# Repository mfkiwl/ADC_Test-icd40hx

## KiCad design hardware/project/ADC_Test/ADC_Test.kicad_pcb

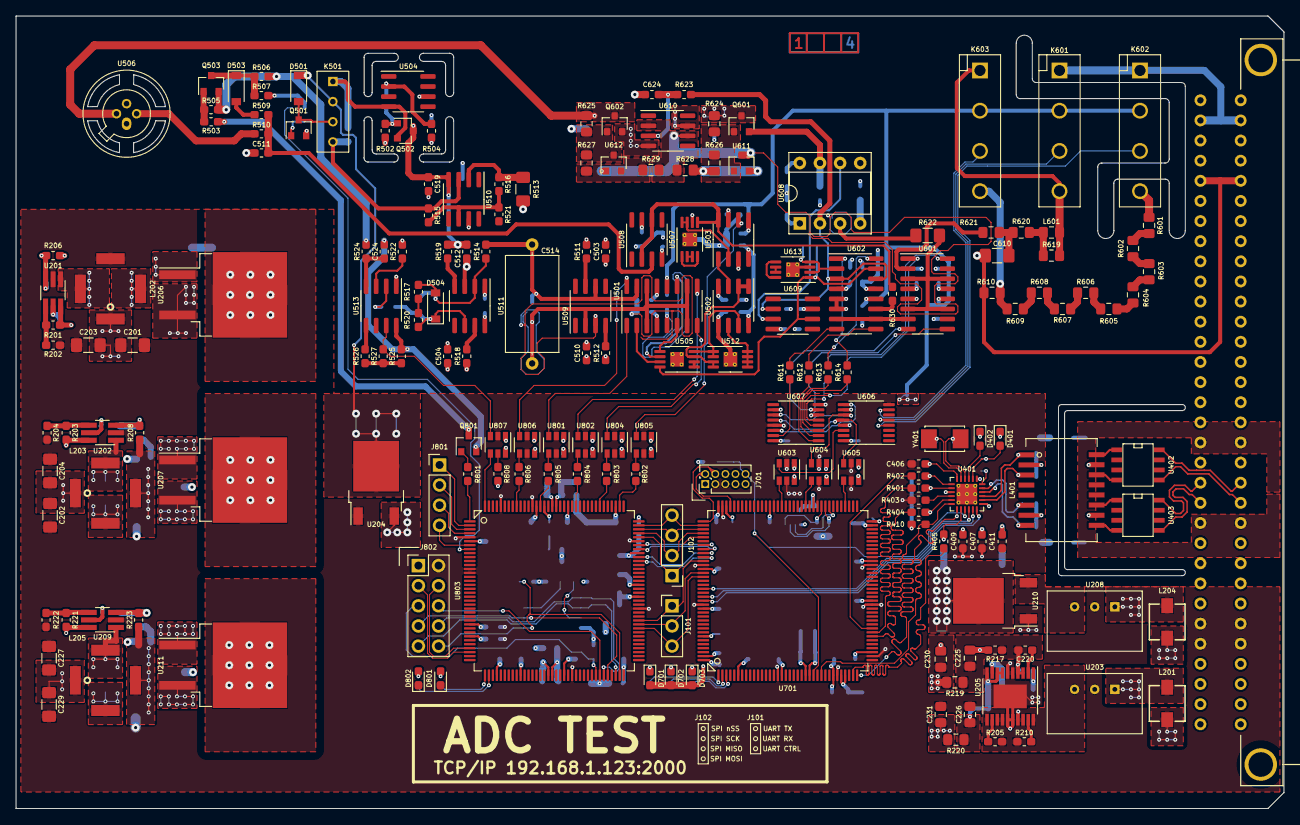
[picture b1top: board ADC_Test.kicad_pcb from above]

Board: 4 copper layers, 160.0 x 100.0 mm, 383 parts (0 on the bottom side), 257 nets.

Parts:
C201, C202, C205, C206, C224, C227, C228: 10u/50V; C_1206_3216Metric_Pad1.42x1.75mm_HandSolder
C203, C204, C216, C217, C218, C219, C222, C223, C229, C243, C244, C245: 4u7/50V; C_1206_3216Metric_Pad1.42x1.75mm_HandSolder
C207, C208, C232, C233, C235, C406, C407, C711, C720: 1u; C_0603_1608Metric_Pad1.05x0.95mm_HandSolder
C209, C210, C238: 1u/HC; C_1206_3216Metric_Pad1.42x1.75mm_HandSolder
C211, C234: 10u/16V; C_1206_3216Metric_Pad1.42x1.75mm_HandSolder
C212, C225, C230, C231, C827, C829: 10u; C_0805_2012Metric_Pad1.15x1.40mm_HandSolder
C213, C241: 47u/16V; C_1206_3216Metric_Pad1.42x1.75mm_HandSolder
C214, C215, C242: 4p7; C_0603_1608Metric_Pad1.05x0.95mm_HandSolder
C220, C221, C239, C240: 10n; C_0603_1608Metric_Pad1.05x0.95mm_HandSolder
C226: 4u7; C_0805_2012Metric_Pad1.15x1.40mm_HandSolder
C236, C237, C402, C405, C408, C409, C410, C411, C412, C502, C503, C504, C505, C506, C507, C508, C509, C510, C511, C512, C513, C516, C517, C518, C519, C520, C523, C524, C601, C602, C603, C604, C605, C606, C607, C608, C609, C611, C612, C613, C614, C615, C616, C617, C618, C619, C620, C621, C622, C623, C701, C702, C703, C705, C708, C710, C712, C713, C714, C715, C716, C717, C718, C719, C721, C801, C802, C803, C804, C805, C806, C807, C808, C809, C810, C811, C812, C813, C814, C815, C816, C817, C818, C819, C820, C821, C822, C823, C824, C825, C826, C828, C830: 100n; C_0603_1608Metric_Pad1.05x0.95mm_HandSolder
C401, C404, C704, C706: 8p; C_0603_1608Metric_Pad1.05x0.95mm_HandSolder
C403: 470p; C_0603_1608Metric_Pad1.05x0.95mm_HandSolder
C413, C414: 1n/1kV; C_1206_3216Metric_Pad1.42x1.75mm_HandSolder
C501: 10p; C_0603_1608Metric_Pad1.05x0.95mm_HandSolder
C514: 23PS222; C_Axial_L12.0mm_D6.5mm_P15.00mm_Horizontal
C515: 2n2/SMD; C_0603_1608Metric_Pad1.05x0.95mm_HandSolder
C521: 33p; C_0603_1608Metric_Pad1.05x0.95mm_HandSolder
C522: DNP; C_0603_1608Metric_Pad1.05x0.95mm_HandSolder
C610: 4n7; C_1206_3216Metric_Pad1.42x1.75mm_HandSolder
C624, C625: 4n7; C_0603_1608Metric_Pad1.05x0.95mm_HandSolder
C707, C709: 2u2; C_0805_2012Metric_Pad1.15x1.40mm_HandSolder
D201, D202, D203: PMEG6010EP,115; D_SOD-128
D401: YELLOW; LED_0603_1608Metric_Pad1.05x0.95mm_HandSolder
D402, D702, D801: GREEN; LED_0603_1608Metric_Pad1.05x0.95mm_HandSolder
D501: 1N4148W; D_SOD-123
D502: BZT585B15TQ-13; D_SOD-523
D503, D504, D505: BAV21W; D_SOD-123
D701, D802: RED; LED_0603_1608Metric_Pad1.05x0.95mm_HandSolder
D703: BLUE; LED_0603_1608Metric_Pad1.05x0.95mm_HandSolder
D803: CDBU0520; D_SOD-523
FB401, FB701: 742792031; L_0805_2012Metric_Pad1.15x1.40mm_HandSolder
J101: Conn_01x03_Male; PinHeader_1x03_P2.54mm_Vertical
J102, J801: Conn_01x04_Male; PinHeader_1x04_P2.54mm_Vertical
J301: C64AC; Socket_DIN41612-CaseC1-AC-Male-64Pin-2rows
J701: 20021111-00010T4LF; PinHeader_2x05_P1.27mm_Vertical
J802: Conn_02x05; PinHeader_2x05_P2.54mm_Vertical
K501: 9012
K601, K602, K603: HE3621A0510; HE360_x-5050462-8
L201, L204: TCK-141
L202, L203, L205: 74489440068
L401: 749010012A
L601: L0805R100MPWRT; R_0805_2012Metric_Pad1.15x1.40mm_HandSolder
Q501, Q503, Q601: BC847; SOT-23
Q502: MMBTA55; SOT-23
Q602, Q801: BC857; SOT-23
R201, R203, R205, R206, R208, R210, R221, R223: 1M; R_0603_1608Metric_Pad1.05x0.95mm_HandSolder
R202, R204, R222: 287k; R_0603_1608Metric_Pad1.05x0.95mm_HandSolder
R207: 82k5; R_0603_1608Metric_Pad1.05x0.95mm_HandSolder
R209: 39k2; R_0603_1608Metric_Pad1.05x0.95mm_HandSolder
R211, R212: 1k6; R_0603_1608Metric_Pad1.05x0.95mm_HandSolder
R213, R214, R226: 120; R_0603_1608Metric_Pad1.05x0.95mm_HandSolder
R215: 357k; R_0603_1608Metric_Pad1.05x0.95mm_HandSolder
R216: 210k; R_0603_1608Metric_Pad1.05x0.95mm_HandSolder
R217, R218, R810, R816: 100; R_0603_1608Metric_Pad1.05x0.95mm_HandSolder
R219, R220: 0R1; R_0805_2012Metric_Pad1.15x1.40mm_HandSolder
R224: 46k4; R_0603_1608Metric_Pad1.05x0.95mm_HandSolder
R225: 1k23; R_0603_1608Metric_Pad1.05x0.95mm_HandSolder
R401, R402, R404, R405: 33; R_0603_1608Metric_Pad1.05x0.95mm_HandSolder
R403, R406, R407, R408, R409, R411, R501, R703, R707: 10k; R_0603_1608Metric_Pad1.05x0.95mm_HandSolder
R410: 1k5; R_0603_1608Metric_Pad1.05x0.95mm_HandSolder
R412: 12k1; R_0603_1608Metric_Pad1.05x0.95mm_HandSolder
R413, R414: 270; R_0603_1608Metric_Pad1.05x0.95mm_HandSolder
R415, R416, R417, R418: 49R9; R_0603_1608Metric_Pad1.05x0.95mm_HandSolder
R419: 1M/1kV; R_1206_3216Metric_Pad1.42x1.75mm_HandSolder
R420, R421: 75/1%; R_0603_1608Metric_Pad1.05x0.95mm_HandSolder
R502, R504: 4k7/.1%; R_0603_1608Metric_Pad1.05x0.95mm_HandSolder
R503, R507: 120k; R_0603_1608Metric_Pad1.05x0.95mm_HandSolder
R505: 620k; R_0603_1608Metric_Pad1.05x0.95mm_HandSolder
R506, R508, R520, R521: 0; R_0603_1608Metric_Pad1.05x0.95mm_HandSolder
R509: 12k; R_0603_1608Metric_Pad1.05x0.95mm_HandSolder
R510, R525: 62/.1%; R_0603_1608Metric_Pad1.05x0.95mm_HandSolder
R511, R512, R518, R519, R524: 10; R_0603_1608Metric_Pad1.05x0.95mm_HandSolder
R513: 6k95/.05%; R_1206_3216Metric_Pad1.42x1.75mm_HandSolder
R514, R623: 12k/.05%; R_0603_1608Metric_Pad1.05x0.95mm_HandSolder
R515, R516: 3k01/.1%; R_0603_1608Metric_Pad1.05x0.95mm_HandSolder
R517: 62k; R_0603_1608Metric_Pad1.05x0.95mm_HandSolder
R522, R630: 620/.05%; R_0603_1608Metric_Pad1.05x0.95mm_HandSolder
R523, R527: 3k9/.05%; R_0603_1608Metric_Pad1.05x0.95mm_HandSolder
R526: 39k/.05%; R_0603_1608Metric_Pad1.05x0.95mm_HandSolder
R601, R602, R603, R604, R605, R606, R607, R608, R609, R610: 1M; R_0805_2012Metric_Pad1.15x1.40mm_HandSolder
R611, R612, R613, R614, R615, R616, R617, R618: 620; R_0603_1608Metric_Pad1.05x0.95mm_HandSolder
R619: 620; R_0805_2012Metric_Pad1.15x1.40mm_HandSolder
R620, R621: 240k/.05%; R_0805_2012Metric_Pad1.15x1.40mm_HandSolder
R622: 22/.1%; R_1206_3216Metric_Pad1.42x1.75mm_HandSolder
R624, R625: 12k; R_0805_2012Metric_Pad1.15x1.40mm_HandSolder
R626, R629: 93k; R_0805_2012Metric_Pad1.15x1.40mm_HandSolder
R627, R628: 39k; R_0805_2012Metric_Pad1.15x1.40mm_HandSolder
R701, R702, R812, R813, R814, R817, R818, R819: 4k7; R_0603_1608Metric_Pad1.05x0.95mm_HandSolder
R704, R706: 680; R_0603_1608Metric_Pad1.05x0.95mm_HandSolder
R705: 560; R_0603_1608Metric_Pad1.05x0.95mm_HandSolder
R801: 6k2; R_0603_1608Metric_Pad1.05x0.95mm_HandSolder
R802, R803, R804, R805, R806: 150; R_0603_1608Metric_Pad1.05x0.95mm_HandSolder
R807, R808, R809: 1k; R_0603_1608Metric_Pad1.05x0.95mm_HandSolder
R811: 22; R_0603_1608Metric_Pad1.05x0.95mm_HandSolder
R815: OPT; R_0603_1608Metric_Pad1.05x0.95mm_HandSolder
U201, U202, U209: LT8330_S6; TSOT-23-6_HandSoldering
U203: TSR1-2490; TSR1
U204: LM1117DTX-5.0/NOPB; TO-252-2
U205: LT3030; ETSSOP-20-1EP_4.4x6.5mm_P0.65mm_EP3x4.2mm
U206: LM317_TO-263; TO-263-2
U207, U211: LM337_TO263; TO-263-2
U208: TSR1-2450; TSR1
U210: LM1117DTX-3.3/NOPB; TO-252-2
U401: LAN8742A; QFN-24-1EP_4x4mm_P0.5mm_EP2.6x2.6mm_ThermalVias
U402, U403: LC03-3.3; SO8E
U501, U601, U602: DG211B; SOIC-16_3.9x9.9mm_P1.27mm
U502: OPA2192; SOIC-8_3.9x4.9mm_P1.27mm
U503: DG419xY; SOIC-8_3.9x4.9mm_P1.27mm
U504: LT1021-7; SOIC-8_3.9x4.9mm_P1.27mm
U505: LT5400-100k-100k; MSOP-8-1EP_3x3mm_P0.65mm_EP1.73x1.85mm_ThermalVias
U506: LM399H; LMx99
U507: LT5400-5k-1k; MSOP-8-1EP_3x3mm_P0.65mm_EP1.73x1.85mm_ThermalVias
U508, U510: OPA177; SOIC-8_3.9x4.9mm_P1.27mm
U509: OPA140; SOIC-8_3.9x4.9mm_P1.27mm
U511: OPA192; SOIC-8_3.9x4.9mm_P1.27mm
U512: LT5400-10k-10k; MSOP-8-1EP_3x3mm_P0.65mm_EP1.73x1.85mm_ThermalVias
U513: LM311; SOIC-8_3.9x4.9mm_P1.27mm
U603, U604, U605, U801, U802, U804, U805, U806, U807: SN74LVC1T45DBV; SOT-23-6
U606, U607: 74HCT595; TSSOP-16_4.4x5mm_P0.65mm
U608: LTC1052; DIP-8_W7.62mm_Socket
U609, U610: AD711; SOIC-8_3.9x4.9mm_P1.27mm
U611, U612: TL431DBZ; SOT-23
U613: LT5400-9k-1k; MSOP-8-1EP_3x3mm_P0.65mm_EP1.73x1.85mm_ThermalVias
U701: STM32H743ZI/STM32F765ZGT6; TQFP-144_20x20mm_P0.5mm
U702: 24LC08B-E/MS; MSOP-8_3x3mm_P0.65mm
U803: ICE40HX4K-TQ144; TQFP-144_20x20mm_P0.5mm
U808: ASDMB-100.000MHZ; Oscillator_SMD_Abracon_ASDMB-4Pin_2.5x2.0mm
U809: MT25QL128ABA1ESE; SOIC-8_5.23x5.23mm_P1.27mm
Y401: NX5032GA-25.000M-LN-CD-1; NX5032GA
Y701: NX3225GD-8MHZ-STD-CRA-3; NX3225GD

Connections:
+1V2: C231.1, C233.1, C237.1, C240.1, C821.1, C822.1, C824.1, C826.1, R220.1, R810.2, R816.2, U803.27, U803.40, U803.92, U803.111
+3.3VF: C241.1, C402.1, C405.1, C606.1, C608.1, C611.1, C701.1, C702.1, C703.1, C705.1, C708.1, C710.1, C711.1, C712.1, C713.1, C714.1, C715.1, C716.1, C717.1, C718.1, C719.1, D701.2, D702.2, D703.2, FB401.2, FB701.2, J701.1, R406.1, R407.1, R408.1, R409.1, R410.1, R701.1, R702.1, R707.1, U210.2, U401.9, U603.6, U604.6, U605.6, U701.6, U701.17, U701.30, U701.39, U701.52, U701.62, U701.72, U701.84, U701.95, U701.108, U701.121, U701.131, U701.143, U701.144, U702.8
+3.3VP: C230.1, C232.1, C236.1, C239.1, C524.1, C807.1, C808.1, C809.1, C810.1, C811.1, C812.1, C813.1, C814.1, C815.1, C816.1, C817.1, C818.1, C819.1, C820.1, C823.1, C825.1, D803.2, Q801.2, R219.1, R525.1, R812.2, R813.2, R814.2, R817.1, R818.1, R819.1, U513.8, U801.6, U802.6, U803.6, U803.30, U803.46, U803.57, U803.72, U803.89, U803.100, U803.123, U803.131, U804.6, U805.6, U806.6, U807.6, U808.1, U808.4, U809.8
+5VF: C213.1, C520.1, C523.1, C603.1, C605.1, C607.1, C609.1, C612.1, C613.1, C614.1, C801.1, C802.1, C803.1, C804.1, C805.1, C806.1, D501.1, K501.2, K601.2, K602.2, K603.2, R808.1, U204.2, U501.12, U503.5, U601.12, U602.12, U603.1, U604.1, U605.1, U606.10, U606.16, U607.10, U607.16, U801.1, U802.1, U804.1, U805.1, U806.1, U807.1
+18VF: C222.1, C502.1, C503.1, C504.1, C505.1, C506.1, C507.1, C508.1, C615.1, C616.1, C618.1, C619.1, Q601.3, R213.1, R504.1, R511.1, R518.1, R624.1, U206.2, U501.13, U502.8, U503.4, U506.3, U508.7, U601.13, U602.13, U609.7
+24VF: C201.1, C202.1, C203.1, C204.1, C205.1, C224.1, C227.1, C229.1, J301.A31, J301.A32, J301.C31, J301.C32, L201.1, L202.1, L203.1, L204.1, L205.1, R201.1, R203.1, R221.1, U201.6, U202.6, U209.6
-14VF: C245.1, C509.1, C510.1, C512.1, C513.1, C516.1, C517.1, C518.1, C519.1, C621.1, C622.1, C623.1, Q502.3, Q503.2, R226.1, R502.2, R505.2, R506.1, R512.2, R519.2, R524.2, U211.3, U501.4, U502.4, U503.7, U508.4, U510.4, U601.4, U602.4, U609.4
-18VF: C223.1, C604.1, Q602.3, R214.1, R625.2, U207.3, U506.4
/ADC/ADIN: C625.2, U505.8, U602.15, U609.6, U613.1
/ADC/FGPA_AD_ID: U501.16, U806.3
/ADC/FGPA_AD_IIN: U501.1, U801.3
/ADC/FGPA_AD_IRN: U501.8, U804.3
/ADC/FGPA_AD_IRP: U501.9, U802.3
/ADC/FPGA_AD_RFS: Q801.3, R503.2
/ADC/FPGA_AD_RFS_OPT: R501.2, U803.8
/ADC/VREF+: U502.7, U505.4, U512.1, U512.2
/ADC/VREF-: U502.1, U502.2, U505.3, U512.3, U512.4
/ADC/VREF_-7V: R630.1, U503.8, U507.5, U508.2, U508.6
/Connector/RX+: J301.A20, U403.8
/Connector/RX-: J301.A21, U403.5
/Connector/TX+: J301.C20, U402.8
/Connector/TX-: J301.C21, U402.5
/Connector/V_HIGH: J301.A2, J301.C2, K601.1, K602.1
/Ethernet/ETH_RXN: L401.8, R418.2, U401.22
/Ethernet/ETH_RXP: L401.6, R417.2, U401.23
/Ethernet/ETH_TXN: L401.3, R416.2, U401.20
/Ethernet/ETH_TXP: L401.1, R415.2, U401.21
/Ethernet/MODE0: R401.1, R406.2, U401.8
/Ethernet/MODE1: R402.1, R407.2, U401.7
/Ethernet/MODE2: R404.1, R408.2, U401.11
/Ethernet/NRST: C721.1, J701.10, R707.2, U401.15, U701.25
/Ethernet/REFCLK0: R405.1, R409.2, U401.14
/Ethernet/REF_CLK: R405.2, U701.35
/Ethernet/RMII_CRS_DV: R404.2, U701.43
/Ethernet/RMII_MDC: U401.13, U701.27
/Ethernet/RMII_MDIO: R410.2, U401.12, U701.36
/Ethernet/RMII_RXD0: R401.2, U701.44
/Ethernet/RMII_RXD1: R402.2, U701.45
/Ethernet/RMII_TXD0: U401.17, U701.128
/Ethernet/RMII_TXD1: U401.18, U701.129
/Ethernet/RMII_TXEN: U401.16, U701.126
/FPGA/100MHZ: R811.1, U803.129
/FPGA/ADC_COMP: R527.2, U513.7, U807.3
/FPGA/AD_ID: R806.2, U806.4
/FPGA/AD_IIN: R805.2, U801.4
/FPGA/AD_IRN: R803.2, U804.4
/FPGA/AD_IRP: R804.2, U802.4
/FPGA/AD_VRH: R802.2, U805.4
/FPGA/COMP: U803.144, U807.4
/FPGA/FGPA_AD_VRH: U503.6, U805.3
/FPGA/FPGA_IO1: U701.117, U803.99
/FPGA/FPGA_IO2: U701.118, U803.98
/FPGA/FPGA_IO3: U701.115, U803.102
/FPGA/FPGA_IO4: U701.116, U803.101
/FPGA/FPGA_SPI3_MISO: J102.2, U701.112, U803.105
/FPGA/FPGA_SPI3_MOSI: J102.1, U701.113, U803.104
/FPGA/FPGA_SPI3_NSS: J102.4, U701.110, U803.107
/FPGA/FPGA_SPI3_SCK: J102.3, U701.111, U803.106
/FPGA/FPGA_UART2_CTRL_TTL: J101.3, U701.123, U803.81
/FPGA/FPGA_UART2_RX_TTL: J101.2, U701.122, U803.82
/FPGA/FPGA_UART2_TX_TTL: J101.1, U701.119, U803.83
/FPGA/GNDPLL0: C829.2, C830.2, U803.53
/FPGA/GNDPLL1: C827.2, C828.2, U803.127
/FPGA/VCCPLL0: C829.1, C830.1, R816.1, U803.54
/FPGA/VCCPLL1: C827.1, C828.1, R810.1, U803.126
/FPGA/iCE_CDONE: J802.5, R817.2, U803.65
/FPGA/iCE_CRESET: J802.6, R812.1, R815.1, U803.66
/FPGA/iCE_MISO: J802.8, U803.67, U809.5
/FPGA/iCE_MOSI: J802.7, U803.68, U809.2
/FPGA/iCE_Rx_TTL: J802.3, U803.34
/FPGA/iCE_SCK: J802.9, R818.2, U803.70, U809.6
/FPGA/iCE_SS_B: J802.10, R819.2, U803.71, U809.1
/FPGA/iCE_Tx_TTL: J802.4, U803.33
/Input/K1_CTR: K601.3, U606.5
/Input/K2_CTR: K602.3, U606.4
/Input/K4_CTR: K603.3, U606.7
/Input/M1_1: R615.1, U601.1
/Input/M1_2: R616.1, U601.16
/Input/M1_3: R617.1, U601.9
/Input/M1_4: R618.1, U601.8
/Input/M2_1: R614.1, U602.1
/Input/M2_2: R613.1, U602.16
/Input/M2_3: R612.1, U602.9
/Input/M2_4: R611.1, U602.8
/Input/SR_CLK: U604.4, U701.86
/Input/SR_DAT: U603.4, U701.92
/Input/SR_LAT: U605.4, U701.76
/MCU/EEPROM_SCL: R702.2, U701.81, U702.6
/MCU/EEPROM_SDA: R701.2, U701.82, U702.5
/MCU/EEPROM_WP: U701.80, U702.7
/MCU/MCU_VDDA: C720.1, FB701.1, U701.32, U701.33
/MCU/TCK_SWCLK: J701.4, U701.109
/MCU/TMS_SWDIO: J701.2, U701.105
AGNDF: C201.2, C202.2, C203.2, C204.2, C205.2, C206.2, C207.2, C208.2, C211.2, C212.2, C213.2, C216.2, C217.2, C218.2, C219.2, C222.2, C223.2, C224.2, C225.2, C226.2, C227.2, C228.2, C229.2, C230.2, C231.2, C232.2, C233.2, C234.2, C235.2, C236.2, C237.2, C239.2, C240.2, C241.2, C243.2, C244.2, C245.2, C401.2, C402.2, C403.2, C404.2, C405.2, C406.2, C407.2, C408.2, C409.2, C410.2, C411.2, C412.2, C413.2, C501.1, C502.2, C503.2, C504.2, C505.2, C506.2, C507.2, C508.2, C509.2, C510.2, C511.2, C512.2, C513.2, C516.2, C517.2, C518.2, C519.2, C520.2, C523.2, C601.2, C602.2, C603.2, C604.2, C605.2, C606.2, C607.2, C608.2, C609.2, C610.1, C611.2, C612.2, C613.2, C614.2, C615.2, C616.2, C618.2, C619.2, C621.2, C622.2, C623.2, C624.2, C701.2, C702.2, C703.2, C704.2, C705.2, C706.2, C707.2, C708.2, C709.2, C710.2, C711.2, C712.2, C713.2, C714.2, C715.2, C716.2, C717.2, C718.2, C719.2, C720.2, C721.2, C801.2, C802.2, C803.2, C804.2, C805.2, C806.2, C807.2, C808.2, C809.2, C810.2, C811.2, C812.2, C813.2, C814.2, C815.2, C816.2, C817.2, C818.2, C819.2, C820.2, C821.2, C822.2, C823.2, C824.2, C825.2, C826.2, D201.1, D203.1, D801.1, D802.1, J301.A5, J301.A27, J301.A28, J301.C5, J301.C27, J301.C28, J701.3, J701.5, J802.2, L202.3, Q501.2, R202.2, R204.2, R207.2, R209.2, R211.2, R212.2, R216.1, R217.2, R218.2, R222.2, R224.2, R225.2, R403.2, R411.2, R412.1, R413.2, R414.2, R419.2, R507.2, R513.2, R522.2, R610.2, R703.2, R815.2, U201.2, U202.2, U203.2, U204.1, U205.5, U205.6, U205.15, U205.16, U205.21, U208.2, U209.2, U210.1, U401.25, U501.5, U502.5, U503.3, U504.6, U505.9, U506.1, U507.6, U507.9, U509.3, U510.7, U511.3, U512.9, U513.1, U601.5, U602.5, U602.6, U603.2, U603.5, U604.2, U604.5, U605.2, U605.5, U606.8, U606.13, U607.8, U607.13, U613.3, U613.9, U701.16, U701.31, U701.38, U701.51, U701.61, U701.83, U701.94, U701.107, U701.120, U701.130, U702.1, U702.2, U702.3, U702.4, U801.2, U801.5, U802.2, U802.5, U803.5, U803.13, U803.14, U803.59, U803.69, U803.86, U803.103, U803.132, U803.140, U804.2, U804.5, U805.2, U805.5, U806.2, U806.5, U807.2, U808.2, U809.4
Earth: C413.1, C414.2, J301.A18, J301.A22, J301.C18, J301.C22, R419.1
unnamed: C206.1, L201.2, U203.1
unnamed: C207.1, U201.5
unnamed: C208.1, U202.5
unnamed: C209.1, D202.2, L202.2
unnamed: C209.2, L202.4, U201.1
unnamed: C210.1, D201.2, L203.2
unnamed: C210.2, L203.4, U202.1
unnamed: C211.1, C212.1, R205.1, R210.1, U203.3, U204.3, U205.11, U205.13, U205.14, U205.17, U205.18, U205.20
unnamed: C214.1, C216.1, C218.1, D202.1, R206.1, U206.3
unnamed: C214.2, R206.2, R207.1, U201.3
unnamed: C215.1, C217.1, C219.1, L203.3, R208.1, U207.2
unnamed: C215.2, R208.2, R209.1, U202.3
unnamed: C220.1, C225.1, R215.1, R217.1, R219.2, U205.3, U205.4
unnamed: C220.2, U205.2
unnamed: C221.1, C226.1, R218.1, R220.2, U205.7, U205.8, U205.10
unnamed: C221.2, U205.9
unnamed: C228.1, L204.2, U208.1
unnamed: C234.1, U208.3, U210.3
unnamed: C235.1, U209.5
unnamed: C238.1, D203.2, L205.2
unnamed: C238.2, L205.4, U209.1
unnamed: C242.1, C243.1, C244.1, L205.3, R223.1, U211.2
unnamed: C242.2, R223.2, R224.1, U209.3
unnamed: C401.1, U401.5, Y401.2
unnamed: C403.1, C406.1, U401.6
unnamed: C404.1, U401.4, Y401.1
unnamed: C414.1, R420.2, R421.2
unnamed: C501.2, Q501.1, R501.1
unnamed: C511.1, R509.1, R510.1, U508.3
unnamed: C514.1, C515.1, R514.2, U501.15, U509.6
unnamed: C514.2, C515.2, U501.3, U501.7, U501.10, U501.14, U509.2
unnamed: C521.1, D504.1, D505.2, R520.1, R523.2, U511.6
unnamed: C521.2, D504.2, D505.1, R514.1, R517.2, U511.2
unnamed: C522.1, U511.1
unnamed: C522.2, U511.8
unnamed: C524.2, R524.1, U513.4
unnamed: C610.2, R620.1, R621.2
unnamed: C617.1, U608.8
unnamed: C620.1, U608.1
unnamed: C624.1, R623.1, U610.3
unnamed: C625.1, U602.2, U613.2, U613.4
unnamed: C704.1, U701.23, Y701.1
unnamed: C706.1, U701.24, Y701.2
unnamed: C707.1, U701.71
unnamed: C709.1, U701.106
unnamed: D401.1, R413.1
unnamed: D401.2, R411.1, U401.2
unnamed: D402.1, R414.1
unnamed: D402.2, U401.3
unnamed: D501.2, K501.3, Q501.3
unnamed: D502.1, R504.2, U504.2
unnamed: D502.2, Q502.1, R502.1
unnamed: D503.1, Q503.3, R506.2, R507.1
unnamed: D503.2, R509.2
unnamed: D701.1, R704.2
unnamed: D702.1, R705.2
unnamed: D703.1, R706.2
unnamed: D801.2, R807.2
unnamed: D802.2, R809.2
unnamed: D803.1, U803.108
unnamed: J801.1, U803.2
unnamed: J801.2, U803.3
unnamed: J801.3, U803.4
unnamed: J801.4, U803.7
unnamed: K501.1, Q502.2, R508.2, U504.4
unnamed: K501.4, R508.1, R510.2, R515.2, U506.2, U510.3
unnamed: K601.4, K603.1, L601.1, R619.2
unnamed: K602.4, R601.2
unnamed: K603.4, R609.1, R610.1
unnamed: L401.9, U403.4
unnamed: L401.10, R420.1
unnamed: L401.11, U403.1
unnamed: L401.14, U402.4
unnamed: L401.15, R421.1
unnamed: L401.16, U402.1
unnamed: L601.2, R619.1, R620.2
unnamed: Q503.1, R503.1, R505.1
unnamed: Q601.1, R624.2, R626.2, U611.1
unnamed: Q602.1, R625.1, R627.2, U612.3
unnamed: Q801.1, R801.1
unnamed: R201.2, R202.1, U201.4
unnamed: R203.2, R204.1, U202.4
unnamed: R205.2, U205.12
unnamed: R210.2, U205.19
unnamed: R211.1, R213.2, U206.1
unnamed: R212.1, R214.2, U207.1
unnamed: R215.2, R216.2, U205.1
unnamed: R221.2, R222.1, U209.4
unnamed: R225.1, R226.2, U211.1
unnamed: R403.1, U401.10
unnamed: R412.2, U401.24
unnamed: R511.2, U509.7
unnamed: R512.1, U509.4
unnamed: R513.1, R516.2, U510.2
unnamed: R515.1, R516.1, R521.2, U510.6
unnamed: R517.1, R520.2
unnamed: R518.2, U511.7
unnamed: R519.1, U511.4
unnamed: R522.1, U513.3
unnamed: R523.1, U513.2
unnamed: R525.2, R526.1, R527.1
unnamed: R526.2, U513.5
unnamed: R601.1, R602.2
unnamed: R602.1, R603.2
unnamed: R603.1, R604.2
unnamed: R604.1, R605.2
unnamed: R605.1, R606.2
unnamed: R606.1, R607.2
unnamed: R607.1, R608.2
unnamed: R608.1, R609.2
unnamed: R611.2, U607.15
unnamed: R612.2, U607.1
unnamed: R613.2, U607.2
unnamed: R614.2, U607.3
unnamed: R615.2, U607.4
unnamed: R616.2, U607.5
unnamed: R617.2, U607.6
unnamed: R618.2, U607.7
unnamed: R621.1, U601.2
unnamed: R622.1, U608.3
unnamed: R622.2, U601.3, U601.6, U601.11, U601.14
unnamed: R623.2, U602.3, U602.14, U608.2, U609.2
unnamed: R626.1, R628.1, U611.2
unnamed: R627.1, R629.2, U612.2
unnamed: R628.2, R629.1, U610.2, U610.6, U611.3, U612.1
unnamed: R630.2, U602.11
unnamed: R703.1, U701.138
unnamed: R704.1, U701.1
unnamed: R705.1, U701.2
unnamed: R706.1, U701.3
unnamed: R801.2, U803.1
unnamed: R802.1, U803.110
unnamed: R803.1, U803.115
unnamed: R804.1, U803.121
unnamed: R805.1, U803.130
unnamed: R806.1, U803.136
unnamed: R807.1, U803.37
unnamed: R808.2, U807.5
unnamed: R809.1, U803.38
unnamed: R811.2, U808.3
unnamed: R813.1, U809.3
unnamed: R814.1, U809.7
unnamed: U501.2, U505.7
unnamed: U501.6, U505.5
unnamed: U501.11, U505.6
unnamed: U502.3, U503.1
unnamed: U502.6, U512.5, U512.6, U512.7, U512.8
unnamed: U503.2, U507.7, U507.8
unnamed: U505.1, U505.2
unnamed: U507.1, U507.4
unnamed: U507.2, U507.3
unnamed: U601.7, U602.7, U602.10
unnamed: U603.3, U606.14
unnamed: U604.3, U606.11, U607.11
unnamed: U605.3, U606.12, U607.12
unnamed: U606.9, U607.14
unnamed: U608.6, U609.3
unnamed: U613.5, U613.8
unnamed: U613.6, U613.7
VCC: C602.1, Q601.2, U608.7, U610.7
VCCQ: C407.1, C408.1, C409.1, C410.1, C411.1, C412.1, FB401.1, L401.2, L401.7, R415.1, R416.1, R417.1, R418.1, U401.1, U401.19
VDD: C601.1, C617.2, C620.2, Q602.2, U608.4, U610.4

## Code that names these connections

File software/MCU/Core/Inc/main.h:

/* USER CODE BEGIN Header */
/**
  ******************************************************************************
  * @file           : main.h
  * @brief          : Header for main.c file.
  *                   This file contains the common defines of the application.
  ******************************************************************************
  * @attention
  *
  * <h2><center>&copy; Copyright (c) 2020 STMicroelectronics.
  * All rights reserved.</center></h2>
  *
  * This software component is licensed by ST under BSD 3-Clause license,
  * the "License"; You may not use this file except in compliance with the
  * License. You may obtain a copy of the License at:
  *                        opensource.org/licenses/BSD-3-Clause
  *
  ******************************************************************************
  */
/* USER CODE END Header */

/* Define to prevent recursive inclusion -------------------------------------*/
#ifndef __MAIN_H
#define __MAIN_H

#ifdef __cplusplus
extern "C" {
#endif

/* Includes ------------------------------------------------------------------*/
#include "stm32f7xx_hal.h"

/* Private includes ----------------------------------------------------------*/
/* USER CODE BEGIN Includes */

/* USER CODE END Includes */

/* Exported types ------------------------------------------------------------*/
/* USER CODE BEGIN ET */

/* USER CODE END ET */

/* Exported constants --------------------------------------------------------*/
/* USER CODE BEGIN EC */

/* USER CODE END EC */

/* Exported macro ------------------------------------------------------------*/
/* USER CODE BEGIN EM */

/* USER CODE END EM */

/* Exported functions prototypes ---------------------------------------------*/
void Error_Handler(void);

/* USER CODE BEGIN EFP */

/* USER CODE END EFP */

/* Private defines -----------------------------------------------------------*/
#define LED_RED_Pin GPIO_PIN_2
#define LED_RED_GPIO_Port GPIOE
#define LED_GREEN_Pin GPIO_PIN_3
#define LED_GREEN_GPIO_Port GPIOE
#define LED_BLUE_Pin GPIO_PIN_4
#define LED_BLUE_GPIO_Port GPIOE
#define SR_LAT_Pin GPIO_PIN_15
#define SR_LAT_GPIO_Port GPIOB
#define EEPROM_WP_Pin GPIO_PIN_11
#define EEPROM_WP_GPIO_Port GPIOD
#define EEPROM_SCL_Pin GPIO_PIN_12
#define EEPROM_SCL_GPIO_Port GPIOD
#define EEPROM_SDA_Pin GPIO_PIN_13
#define EEPROM_SDA_GPIO_Port GPIOD
#define SR_CLK_Pin GPIO_PIN_15
#define SR_CLK_GPIO_Port GPIOD
#define SR_DAT_Pin GPIO_PIN_7
#define SR_DAT_GPIO_Port GPIOG
#define SP3_NSS_Pin GPIO_PIN_15
#define SP3_NSS_GPIO_Port GPIOA
#define FPGA_IO3_Pin GPIO_PIN_1
#define FPGA_IO3_GPIO_Port GPIOD
#define FPGA_IO4_Pin GPIO_PIN_2
#define FPGA_IO4_GPIO_Port GPIOD
#define FPGA_IO1_Pin GPIO_PIN_3
#define FPGA_IO1_GPIO_Port GPIOD
#define FPGA_IO2_Pin GPIO_PIN_4
#define FPGA_IO2_GPIO_Port GPIOD
/* USER CODE BEGIN Private defines */

#define		CAL_PREDEF_1VO		-0.0000853
#define		CAL_PREDEF_1VG		0.9854553//0.985355
#define		CAL_PREDEF_10VO		-0.000076
#define		CAL_PREDEF_10VG		0.9854889//0.985485
#define		CAL_PREDEF_100VO	-0.000462
#define		CAL_PREDEF_100VG	0.98400996//0.984012
#define		CAL_PREDEF_NZO		-170.0
#define		CAL_PREDEF_STEP		38500

#define	SR_M14		0x80
#define	SR_M13		0x40
#define	SR_M12		0x20
#define	SR_M11		0x10
#define	SR_M21		0x08
#define	SR_M22		0x04
#define	SR_M23		0x02
#define	SR_M24		0x01
#define	SR_K4		0x80
#define	SR_K1		0x20
#define	SR_K2		0x10

#define	SR_INVERT_MASK	0xFF

#define STRUCT_SIZE 72

#pragma pack(push, 1)

union cal_data
{
	struct cal_struct
	{
	int32_t	adc_z_offset;
	int32_t	adc_step;
	double	v_1V_offset;
	double	v_1V_gain;
	double	v_10V_offset;
	double	v_10V_gain;
	double	v_100V_offset;
	double	v_100V_gain;
	}structure;

	uint8_t bytes[STRUCT_SIZE];
};


#pragma pack(pop)

enum zero_states
{
	ZERO_OFF = 0,
	ZERO_ON,
	ZERO_ONCE
};

enum measure_mode
{
	AUTO_ZERO = 1,
	NORM_MEAS,
	ADC_MEAS

};
struct cfg_struct
{
	uint32_t range;
	uint8_t range_index;
	uint8_t nplc_index;
	uint32_t samples;
	uint8_t nplc;
	uint8_t zero_status;
	double zero_val;
	double adc_raw[7];
	double adc_cf[7];
	uint8_t adc_nplc[7];
	uint8_t zero_done;
	union cal_data calibration;
};

typedef enum
{
  BSP_OK       = 0x00U,
  BSP_ERROR    = 0x01U,
  BSP_BUSY = 0x02U,
  BSP_TIMEOUT  = 0x03U,
  BSP_EEPROM_EMPTY = 0x04U,
  BSP_EEPROM_MAX_SIZE = 0x05U,
  BSP_EEPROM_NO_CONNECTION = 0x06U,
  BSP_EEPROM_WRITE_ERROR = 0x07U,
  BSP_EEPROM_READ_ERROR = 0x08U

} BSP_StatusTypeDef;


BSP_StatusTypeDef eeprom_read(uint8_t* data, size_t size);
BSP_StatusTypeDef eeprom_write(uint8_t* data, size_t size);
BSP_StatusTypeDef eeprom_status();
/* USER CODE END Private defines */

#ifdef __cplusplus
}
#endif

#endif /* __MAIN_H */

/************************ (C) COPYRIGHT STMicroelectronics *****END OF FILE****/

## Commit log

2020-10-06 Added doc
2020-10-06 Schematic
2020-10-08 Development
2020-10-08 Schematic design.
2020-10-08 Calculated voltages for the voltage sources.
2020-10-08 Replaced TL061 with AD711.
2020-10-08 Schematic, PCB and BOM.
2020-10-09 Changes in documentation, schematics and PCB.
2020-10-11 PCB design
2020-10-11 PCB design.
2020-10-12 PCB layout almost done.
2020-10-12 PCB design done.
2020-10-13 Added STM32 project.
2020-11-01 FPGA and MCU runs.
2020-11-03 MCU readout from FPGA works.
2020-11-06 Problems with data from FPGA.
2020-11-07 ADC works.
2020-11-08 MCU software development
2020-11-08 MCU sofware development.
2020-11-09 Modified the measurement functions. PCB ready for calibration.
2020-11-10 Calibrated ADC with a Inmel 7000 calibrator. Gain and offset values are in main.h.
